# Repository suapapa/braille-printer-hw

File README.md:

# Hardware for Braille Label Printer

- sch : schemetic(.sch) and artwork(.brd) made by EagleCad-6
- cad : drawing for laser cut acrylic case made by Librecad
- arduino : arduino sketch

# License

The sch, cad and arduino sketch follow GNU-GPL.

    Copyright (c) 2012 Homin Lee <homin.lee@suapapa.net>. All right reserved.

    This is free software; you can redistribute it and/or
    modify it under the terms of the GNU Lesser General Public
    License as published by the Free Software Foundation; either
    version 2.1 of the License, or (at your option) any later version.

    This library is distributed in the hope that it will be useful,
    but WITHOUT ANY WARRANTY; without even the implied warranty of
    MERCHANTABILITY or FITNESS FOR A PARTICULAR PURPOSE.  See the GNU
    Lesser General Public License for more details.

    You should have received a copy of the GNU Lesser General Public
    License along with this library; if not, write to the Free Software
    Foundation, Inc., 51 Franklin St, Fifth Floor, Boston, MA  02110-1301  USA

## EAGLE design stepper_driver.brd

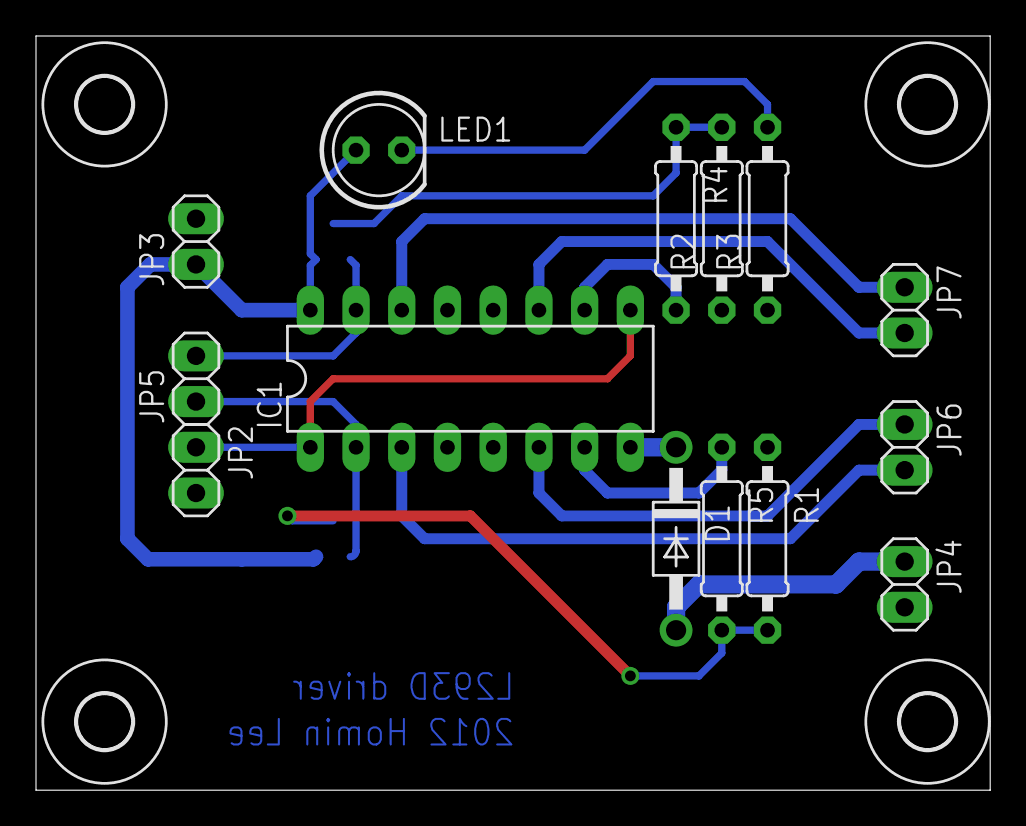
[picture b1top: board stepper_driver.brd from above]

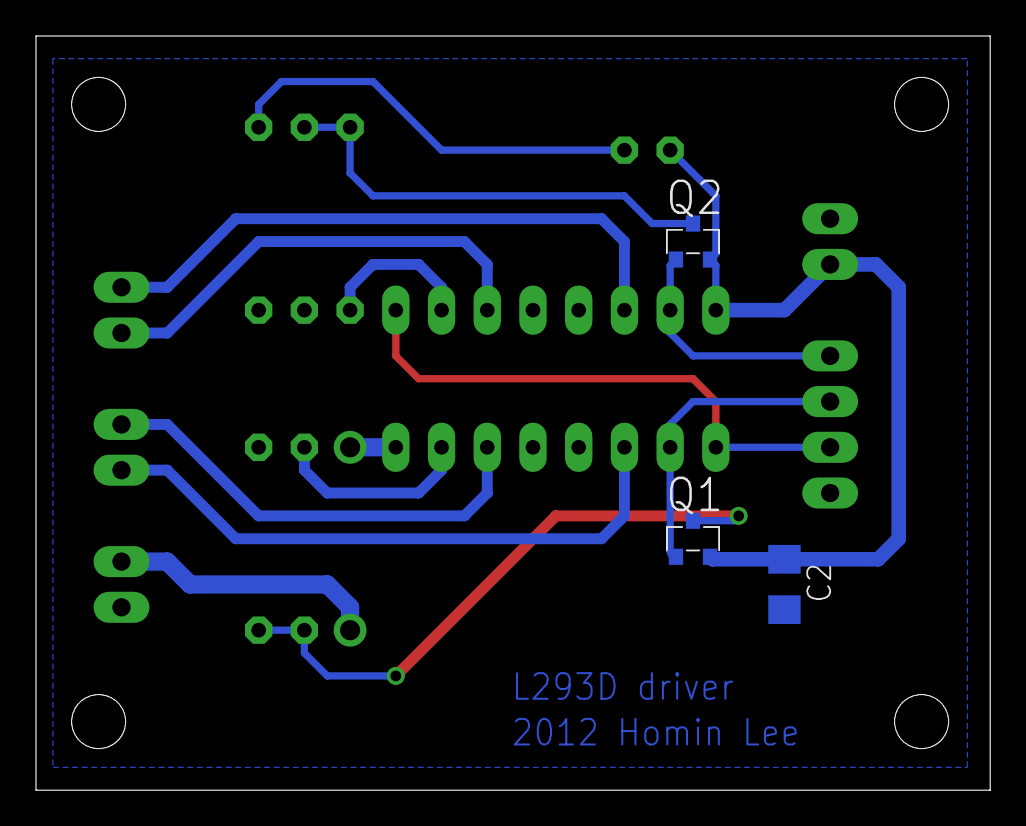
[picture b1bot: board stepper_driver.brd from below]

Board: 2 copper layers, 53.0 x 41.9 mm, 21 parts (3 on the bottom side), 16 nets.

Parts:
C2: C1206
D1: 1N4004; DO41-10
IC1: L293D; DIL16
JP2, JP3, JP4, JP5, JP6, JP7: 1X02
LED1: LED5MM
Q1, Q2: IRLML5203; MICRO3
R1, R2: 10k; 0207/10
R3, R4, R5: 1k; 0207/10
U$6, U$7, U$8, U$9: 3,0

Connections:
5V: C2.1, IC1.16, JP3.1, LED1.A, Q1.2, Q2.2
GND: C2.2, IC1.4, IC1.5, IC1.12, IC1.13, JP3.2, JP4.2, R1.1, R2.1, R3.1
IC1_EN: IC1.1, IC1.9, JP2.1
unnamed: IC1.3, JP6.2
unnamed: IC1.6, JP6.1
unnamed: IC1.11, JP7.2
unnamed: IC1.14, JP7.1
unnamed: IC1.7, R5.1
unnamed: D1.C, IC1.8
unnamed: IC1.10, R4.2
unnamed: LED1.K, R3.2
unnamed: Q1.3, R1.2, R5.2
unnamed: Q2.3, R2.2, R4.1
S1: IC1.2, JP5.1, Q1.1
S2: IC1.15, JP5.2, Q2.1
VCC: D1.A, JP4.1

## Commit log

2012-09-28 Initial import of BraillePrinter HW
2012-09-28 First draft artwork done
2012-09-28 Polishing artwork
2012-10-05 Fix to only for single L293D IC
2012-10-06 cad: add blueprint for feeder
2012-10-13 cad: split cad drawing to 1t and 5t. following it's t dimention
2012-10-13 cad: fixed drawing
2012-10-30 cad: fixed 5t acril
2012-10-30 cad: removed unused parts from acril 5t
2012-11-07 Rework laser cutting
2012-11-07 cad: more fixes
2012-11-10 Testing serial and stepper
2012-11-10 arduino: fill up draft codes
2012-11-10 arduino: add script to test protocol
2012-11-12 arduino: add codes for servos
2012-11-12 arduino: add codes for lcd
2012-11-12 arduino: put it all together
2012-11-12 arduino: put all servos to release position after init servos
2012-11-12 arduino: clean up code
2012-11-12 Add files which made by arduino build to .gitignore
2012-11-12 moved eaglecad files to a directory, eaglecad
2012-11-12 arduino: fix pinmaps
2012-11-12 arduino: fixed to use working gpio
2012-11-16 arduino: fix servo's pin and direction
2012-11-16 arduino: fix pinmap, trasition on backlight
2012-11-16 arduino: add scripts
    - blp_server.py: UDS server to Braille Label Printer
    - blp_server_test.py: simple script to test blp_server.py
    - blp_test.py: simple script to test Braille Label Printer via serial
2012-11-16 arduino: Fix not to send OK back
    Make it simple, simple, simple...
2012-11-17 arduino: hot fix in ghackfair
